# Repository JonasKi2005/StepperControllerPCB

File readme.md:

# 6-Axis Robot Arm — Firmware (v1: ESP32-S3 + TMC2209)

Firmware for a custom 3D-printed 6-axis robotic arm (~50 cm reach, 2 kg payload).
This is the **first-generation control board**, built around an **ESP32-S3** carrier
PCB driving **six TMC2209** stepper drivers, with a WiFi web UI for manual control
and bring-up.

> **Status:** This is the original ESP32-S3 board and is **retired**. It served as the
> first working bring-up of the arm, but the fabricated PCB had a UART addressing
> limitation (the driver address-select pins were not broken out as intended, so the
> address-multiplexing scheme below could not be used as designed). Development has
> since moved to a custom STM32G484 + TMC5240 board. This repo is kept as a reference
> for the working step-generation and driver code.

---

## Hardware

| Component       | Part                                            |
| --------------- | ----------------------------------------------- |
| MCU             | ESP32-S3 (DevKitC-class carrier PCB)            |
| Stepper drivers | 6× TMC2209 (BTT V1.2 modules, R_sense = 0.11 Ω) |
| Motors J1–J3    | NEMA 17 `17HS19-2004S1` (2 A)                   |
| Motors J4–J6    | NEMA 17 `17HS13-0404S` (0.4 A, short body)      |
| Power           | 24 V supply → drivers; logic rails on-board     |

### Driver bus layout

The six drivers are split across **two UART buses**, three drivers per bus, using
the TMC2209's single-wire half-duplex UART with **address multiplexing** (each driver
on a bus is assigned address 0, 1, or 2):

```
UART1 ──┬── J1 (addr 0)      UART2 ──┬── J4 (addr 0)
        ├── J2 (addr 1)              ├── J5 (addr 1)
        └── J3 (addr 2)              └── J6 (addr 2)
```

All six drivers share a single **EN line**. The arm boots **disarmed** (EN held HIGH,
motors freewheeling) and only energizes after a POST to `/arm`.

---

## Firmware architecture

Built on **ESP-IDF (FreeRTOS)**. Four main translation units:

### `main.cpp` — entry point

Boot sequence: NVS init → construct one `TMC2209` per axis (UART + GPIO setup only) →
optionally push register config to each driver → start the motion controller →
bring up WiFi (the web server starts automatically once an IP is assigned). All pin
assignments and per-joint parameters (current, microsteps) live here in one place.

### `TMC2209.cpp` — driver class

Low-level UART register access with CRC, plus higher-level config:

- **`write_reg` / `read_reg`** — 8-byte datagrams, CRC-checked, with echo handling for
  single-wire half-duplex.
- **`init()`** — pushes GCONF/CHOPCONF/IHOLD_IRUN/PWMCONF and **verifies writes landed**
  by checking that `IFCNT` incremented by the expected count (your UART-wiring smoke test).
- **`set_current()`** — computes IRUN/IHOLD from a requested RMS current, automatically
  selecting `vsense` for best resolution.
- **`set_microsteps()`** — maps microstep count to the CHOPCONF MRES field.
- **`print_drv_status()`** — decodes DRV_STATUS flags (overtemp, short, open-load, etc.).

### `MotorController.cpp` — motion engine

The ESP32-S3 has only 4 hardware GPTimers, so **one timer per axis is impossible**.
Instead a **single shared timer fires at 20 kHz**, and the ISR uses **Bresenham-style
step accumulation** (the same pattern Marlin/Klipper use): each active axis accumulates
its `velocity_sps` per tick and emits a step pulse when the accumulator crosses the tick
rate. Supports per-axis jogging, absolute `move_to` targets, and clean stop/disarm.
Commands flow through a FreeRTOS queue to a dedicated motion task pinned to core 1.

### `Server.cpp` — WiFi + web UI

Connects as a WiFi station and serves a self-contained HTML control panel (no external
assets). The UI polls `/status` for live position and arm state, and exposes jog,
move-to, arming, current, and microstep controls.

#### HTTP API

| Method | Endpoint      | Params                | Purpose                                             |
| ------ | ------------- | --------------------- | --------------------------------------------------- |
| GET    | `/`           | —                     | Web control UI                                      |
| GET    | `/status`     | —                     | JSON: arm state, per-axis step counts, moving flags |
| POST   | `/arm`        | —                     | Energize drivers (EN low)                           |
| POST   | `/disarm`     | —                     | De-energize drivers (EN high)                       |
| POST   | `/stop_all`   | —                     | Stop all axes                                       |
| POST   | `/jog`        | `axis`, `dir`, `v`    | Continuous jog until stop                           |
| POST   | `/stop`       | `axis`                | Stop one axis                                       |
| POST   | `/move_to`    | `axis`, `target`, `v` | Move one axis to a step target                      |
| POST   | `/current`    | `axis`, `ma`          | Set RMS current (50–2000 mA)                        |
| POST   | `/microsteps` | `axis`, `us`          | Set microstepping (1…256)                           |

---

## Building & flashing

Requires the **ESP-IDF** toolchain. From the firmware directory:

```bash
idf.py set-target esp32s3
idf.py build
idf.py -p <PORT> flash monitor
```

On macOS the ESP32-S3 enumerates via the **Silicon Labs CP210x** driver; `<PORT>` is
typically `/dev/cu.SLAB_USBtoUART` or similar.

Set your WiFi credentials (`WIFI_SSID` / `WIFI_PASS`) before building. On boot the
serial monitor prints the assigned IP address — open it in a browser to reach the UI.

> **Bring-up note:** Driver `init()` is commented out in `main.cpp` by default so the
> board can boot and run the web UI without working UART to the drivers. Re-enable it
> once the UART wiring is verified — `init()` will report via `IFCNT` whether register
> writes are actually reaching each driver.

---

## Known limitations of this board

- **UART addressing:** the address-multiplexing scheme above depends on each driver's
  address-select pins being individually set. On the fabricated board this wasn't the
  case and has to be fixed in the kicad files.
- No closed-loop feedback — purely open-loop step counting.
- This is my first PCB so there probably will be some other errors, since the PCB wasn't tested so far.

---

## A note on the code

**The code in this repository is handwritten.** AI was used only to polish and comment
it — the architecture, logic, and implementation decisions are my own.

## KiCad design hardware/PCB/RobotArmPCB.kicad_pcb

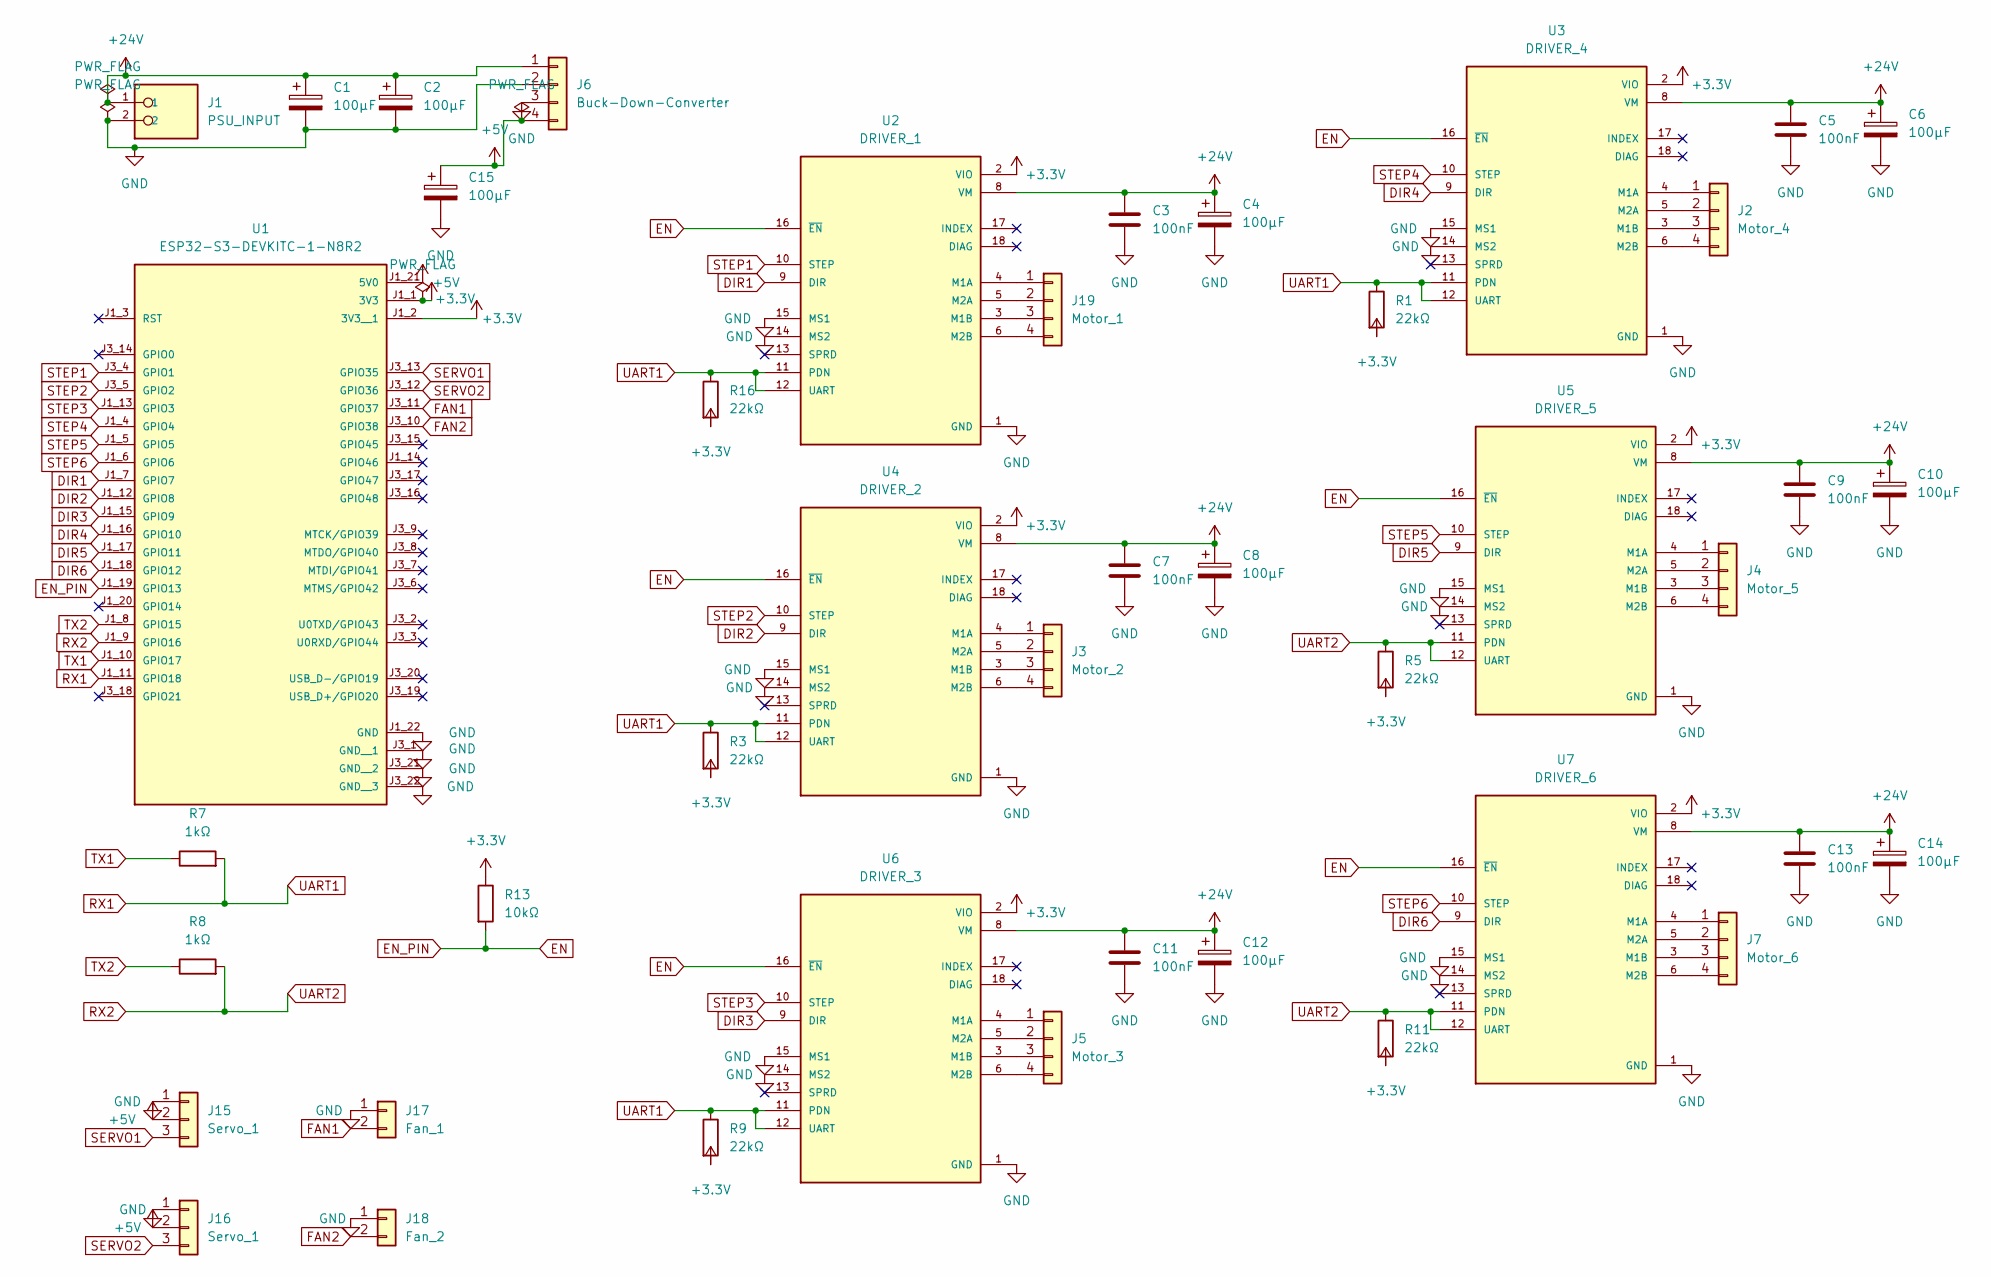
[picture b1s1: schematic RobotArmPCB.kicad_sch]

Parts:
C1, C2, C4, C6, C8, C10, C12, C14, C15: 100µF; CP_Radial_D6.3mm_P2.50mm
C3, C5, C7, C9, C11, C13: 100nF; C_Disc_D5.0mm_W2.5mm_P2.50mm
J1: PSU_INPUT; PHOENIX_1935161; PARTREV 14.12.2022
J2: Motor_4; JST_XH_B4B-XH-A_1x04_P2.50mm_Vertical
J3: Motor_2; JST_XH_B4B-XH-A_1x04_P2.50mm_Vertical
J4: Motor_5; JST_XH_B4B-XH-A_1x04_P2.50mm_Vertical
J5: Motor_3; JST_XH_B4B-XH-A_1x04_P2.50mm_Vertical
J6: Buck-Down-Converter; YAAJ_DCDC_StepDown_LM2596
J7: Motor_6; JST_XH_B4B-XH-A_1x04_P2.50mm_Vertical
J15, J16: Servo_1; PinHeader_1x03_P2.54mm_Vertical
J17: Fan_1; PinHeader_1x02_P2.54mm_Vertical
J18: Fan_2; PinHeader_1x02_P2.54mm_Vertical
J19: Motor_1; JST_XH_B4B-XH-A_1x04_P2.50mm_Vertical
R1, R3, R5, R9, R11, R16: 22kΩ; R_Axial_DIN0207_L6.3mm_D2.5mm_P7.62mm_Horizontal
R7, R8: 1kΩ; R_Axial_DIN0207_L6.3mm_D2.5mm_P7.62mm_Horizontal
R13: 10kΩ; R_Axial_DIN0207_L6.3mm_D2.5mm_P7.62mm_Horizontal
U1: ESP32-S3-DEVKITC-1-N8R2; XCVR_ESP32-S3-DEVKITC-1-N8R2; PARTREV V1
U2: DRIVER_1; MODULE_TMC2209_SILENTSTEPSTICK; PARTREV 1.20
U3: DRIVER_4; MODULE_TMC2209_SILENTSTEPSTICK; PARTREV 1.20
U4: DRIVER_2; MODULE_TMC2209_SILENTSTEPSTICK; PARTREV 1.20
U5: DRIVER_5; MODULE_TMC2209_SILENTSTEPSTICK; PARTREV 1.20
U6: DRIVER_3; MODULE_TMC2209_SILENTSTEPSTICK; PARTREV 1.20
U7: DRIVER_6; MODULE_TMC2209_SILENTSTEPSTICK; PARTREV 1.20

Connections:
+3.3V: R1.2, R3.2, R5.2, R9.2, R11.2, R13.1, R16.2, U1.J1_1 (3V3), U1.J1_2 (3V3__1), U2.2 (VIO), U3.2 (VIO), U4.2 (VIO), U5.2 (VIO), U6.2 (VIO), U7.2 (VIO)
+5V: C15.1, J6.4, J15.2, J16.2, U1.J1_21 (5V0)
+24V: C1.1, C2.1, C3.1, C4.1, C5.1, C6.1, C7.1, C8.1, C9.1, C10.1, C11.1, C12.1, C13.1, C14.1, J1.1, J6.1, U2.8 (VM), U3.8 (VM), U4.8 (VM), U5.8 (VM), U6.8 (VM), U7.8 (VM)
DIR1: U1.J1_7 (GPIO7), U2.9 (DIR)
DIR2: U1.J1_12 (GPIO8), U4.9 (DIR)
DIR3: U1.J1_15 (GPIO9), U6.9 (DIR)
DIR4: U1.J1_16 (GPIO10), U3.9 (DIR)
DIR5: U1.J1_17 (GPIO11), U5.9 (DIR)
DIR6: U1.J1_18 (GPIO12), U7.9 (DIR)
EN: R13.2, U1.J1_19 (GPIO13), U2.16 (~EN), U3.16 (~EN), U4.16 (~EN), U5.16 (~EN), U6.16 (~EN), U7.16 (~EN)
FAN1: J17.2, U1.J3_11 (GPIO37)
FAN2: J18.2, U1.J3_10 (GPIO38)
GND: C1.2, C2.2, C3.2, C4.2, C5.2, C6.2, C7.2, C8.2, C9.2, C10.2, C11.2, C12.2, C13.2, C14.2, C15.2, J1.2, J6.2, J6.3, J15.1, J16.1, J17.1, J18.1, U1.J1_22 (GND), U1.J3_1 (GND__1), U1.J3_21 (GND__2), U1.J3_22 (GND__3), U2.1 (GND), U2.7 (GND), U2.14 (MS2), U2.15 (MS1), U3.1 (GND), U3.7 (GND), U3.14 (MS2), U3.15 (MS1), U4.1 (GND), U4.7 (GND), U4.14 (MS2), U4.15 (MS1), U5.1 (GND), U5.7 (GND), U5.14 (MS2), U5.15 (MS1), U6.1 (GND), U6.7 (GND), U6.14 (MS2), U6.15 (MS1), U7.1 (GND), U7.7 (GND), U7.14 (MS2), U7.15 (MS1)
unnamed: J2.1, U3.4 (M1A)
unnamed: J2.2, U3.5 (M2A)
unnamed: J2.3, U3.3 (M1B)
unnamed: J2.4, U3.6 (M2B)
unnamed: J3.1, U4.4 (M1A)
unnamed: J3.2, U4.5 (M2A)
unnamed: J3.3, U4.3 (M1B)
unnamed: J3.4, U4.6 (M2B)
unnamed: J4.1, U5.4 (M1A)
unnamed: J4.2, U5.5 (M2A)
unnamed: J4.3, U5.3 (M1B)
unnamed: J4.4, U5.6 (M2B)
unnamed: J5.1, U6.4 (M1A)
unnamed: J5.2, U6.5 (M2A)
unnamed: J5.3, U6.3 (M1B)
unnamed: J5.4, U6.6 (M2B)
unnamed: J7.1, U7.4 (M1A)
unnamed: J7.2, U7.5 (M2A)
unnamed: J7.3, U7.3 (M1B)
unnamed: J7.4, U7.6 (M2B)
unnamed: J19.1, U2.4 (M1A)
unnamed: J19.2, U2.5 (M2A)
unnamed: J19.3, U2.3 (M1B)
unnamed: J19.4, U2.6 (M2B)
RX1: R1.1, R3.1, R7.2, R9.1, R16.1, U1.J1_11 (GPIO18), U2.11 (PDN), U2.12 (UART), U3.11 (PDN), U3.12 (UART), U4.11 (PDN), U4.12 (UART), U6.11 (PDN), U6.12 (UART)
RX2: R5.1, R8.2, R11.1, U1.J1_9 (GPIO16), U5.11 (PDN), U5.12 (UART), U7.11 (PDN), U7.12 (UART)
SERVO1: J15.3, U1.J3_13 (GPIO35)
SERVO2: J16.3, U1.J3_12 (GPIO36)
STEP1: U1.J3_4 (GPIO1), U2.10 (STEP)
STEP2: U1.J3_5 (GPIO2), U4.10 (STEP)
STEP3: U1.J1_13 (GPIO3), U6.10 (STEP)
STEP4: U1.J1_4 (GPIO4), U3.10 (STEP)
STEP5: U1.J1_5 (GPIO5), U5.10 (STEP)
STEP6: U1.J1_6 (GPIO6), U7.10 (STEP)
TX1: R7.1, U1.J1_10 (GPIO17)
TX2: R8.1, U1.J1_8 (GPIO15)

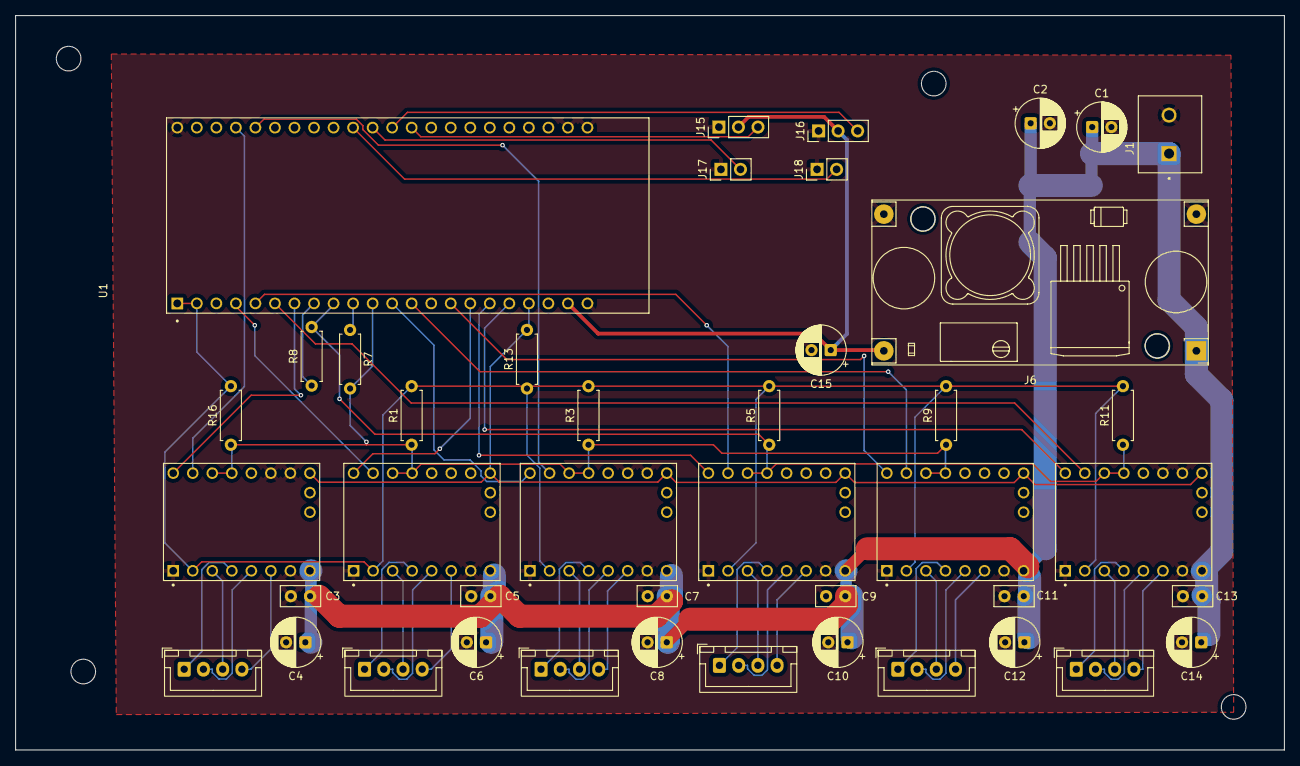
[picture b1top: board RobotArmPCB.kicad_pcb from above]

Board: 2 copper layers, 165.0 x 95.5 mm, 43 parts (0 on the bottom side), 49 nets.

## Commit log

2026-06-24 Stop tracking KiCad .history folder; add to gitignore
2026-06-24 added readme
